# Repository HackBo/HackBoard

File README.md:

HackBoard

Arduino Leonardo compatible board

Un Arduino engallado para hacer mas fáciles y rápidos tus desarrollos. 

Diseñado por y para Geeks . . .

Preview
=========
![Front](
https://github.com/HackBo/HackBoard/blob/master/img/HackBoard.png)

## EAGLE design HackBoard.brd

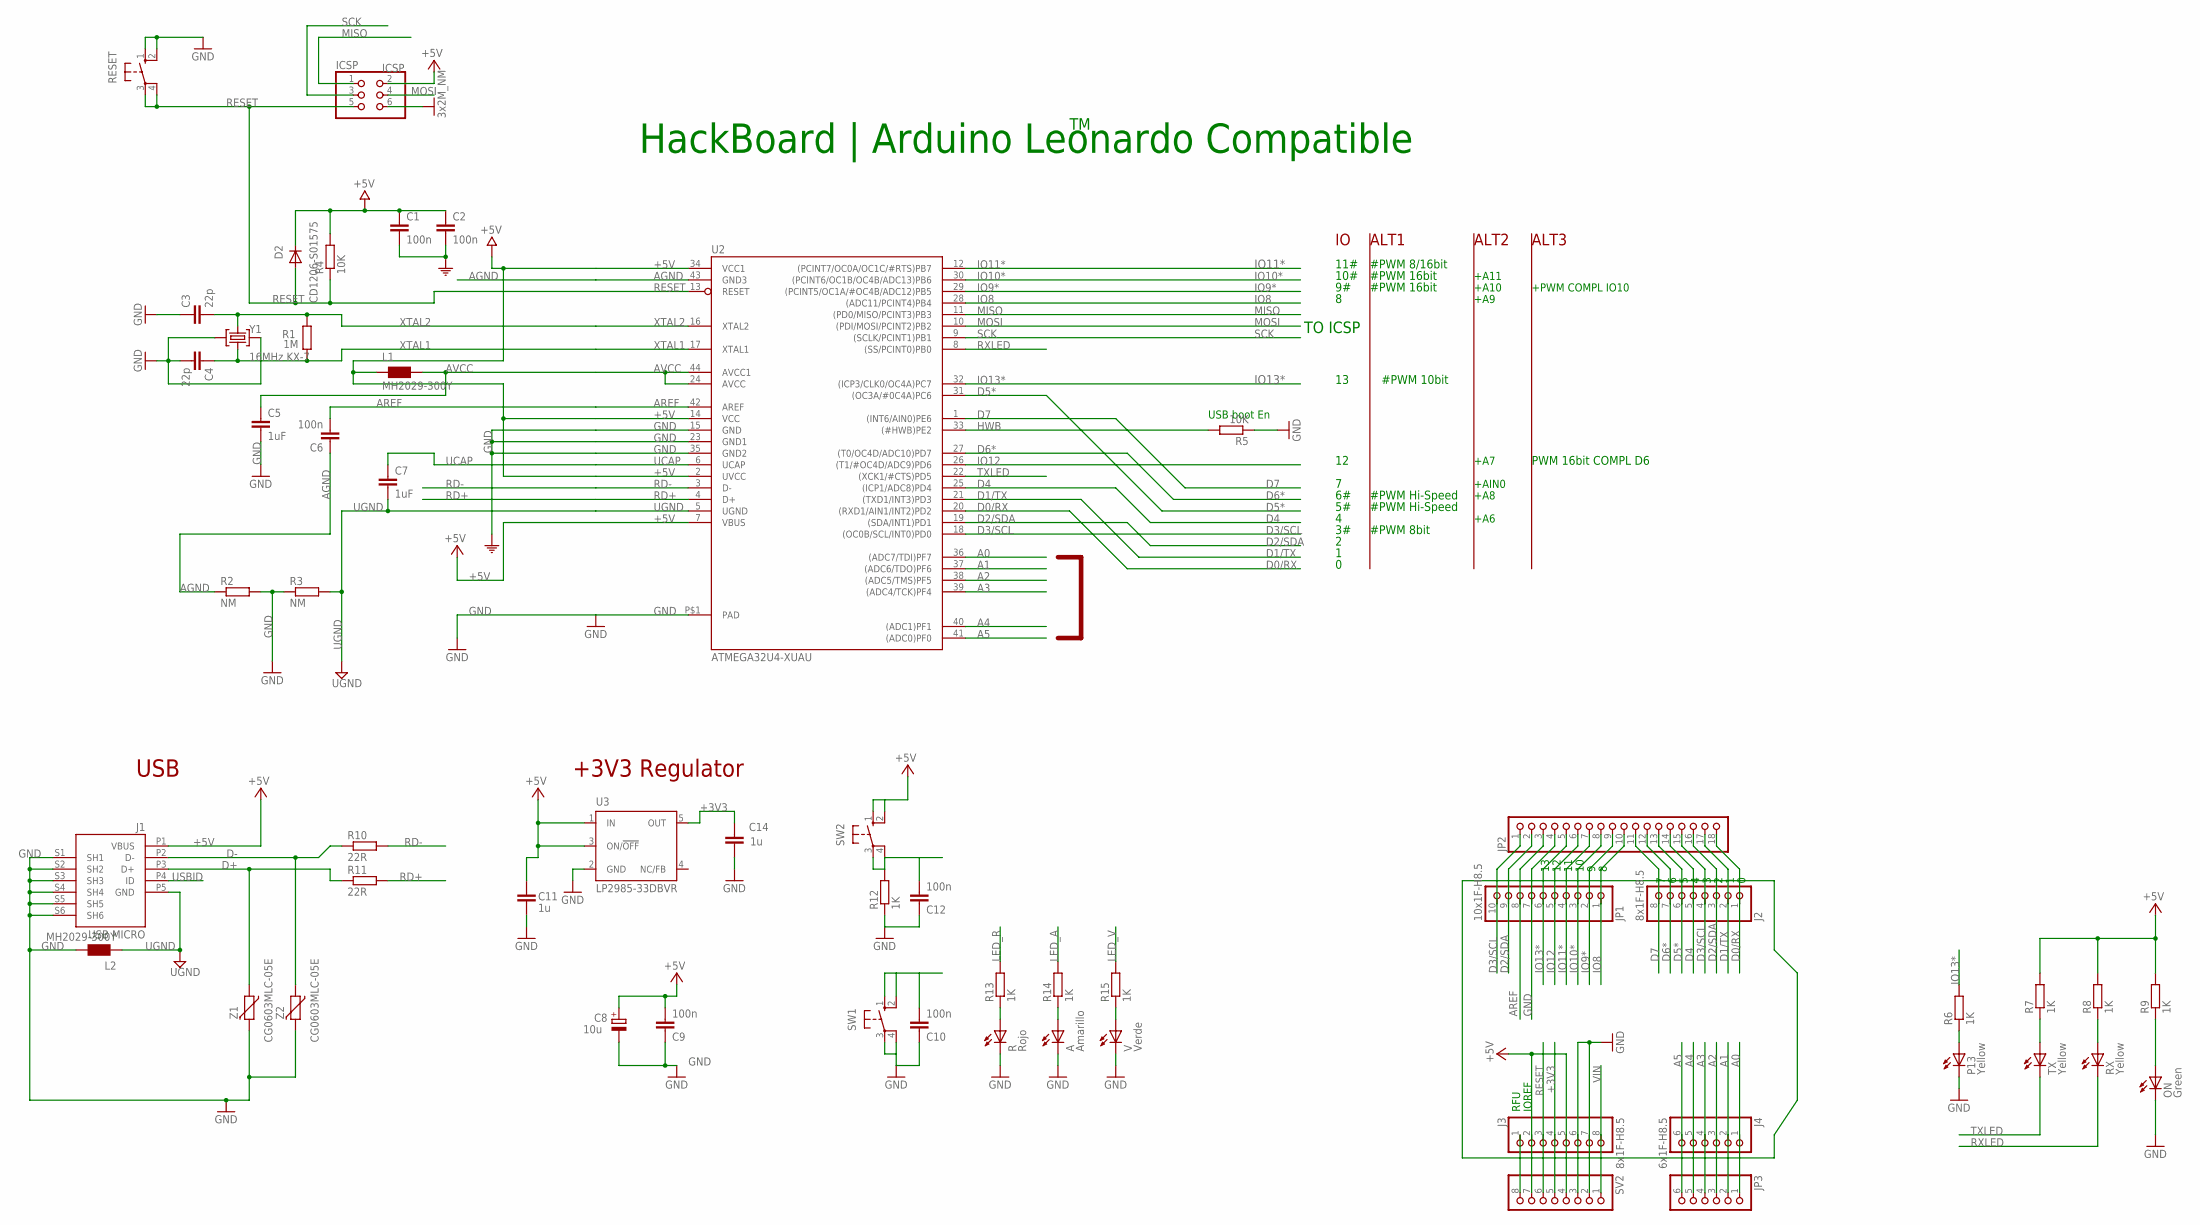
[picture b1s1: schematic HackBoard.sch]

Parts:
A: Amarillo; CHIPLED_0805
C1, C2, C6, C9, C10, C12: 100n; C0805
C3, C4: 22p; C0603-ROUND
C5, C7: 1uF; C0603-ROUND
C8: 10u; SMC_B
C11, C14: 1u; C0603-ROUND
D2: CD1206-S01575; MINIMELF
ICSP: ICSP; 2X03
J1: USB MICRO; CON2_USB_MICRO_B_AT
J2, J3: 8x1F-H8.5; 1X08
J4: 6x1F-H8.5; 1X06
JP1: 10x1F-H8.5; 1X10
JP2: PINHD-1X18; 1X18
JP3: PINHD-1X6; 1X06
L1, L2: MH2029-300Y; 0805
ON: Green; CHIPLED_0805
P13: Yellow; CHIPLED_0805
R: Rojo; CHIPLED_0805
R1: 1M; R0603-ROUND
R2, R3: NM; R0402
R4, R5: 10K; R0805
R6, R7, R8, R9, R12, R13, R14, R15: 1K; M0805
R10, R11: 22R; M0805
RESET: 10-XX; B3F-10XX
RX: Yellow; CHIPLED_0805
SV2: PINHD-1X8; 1X08
SW1, SW2: 10-XX; B3F-10XX
TX: Yellow; CHIPLED_0805
U2: ATMEGA32U4-XUAU; TQFP44-PAD
U3: LP2985-33DBVR; SOT23-DBV
V: Verde; CHIPLED_0805
Y1: 16MHz KX-7; CRYSTAL-3.2-2.5
Z1, Z2: CG0603MLC-05E; CT/CN0603

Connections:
+3V3: C14.2, J3.4, SV2.5, U3.5 (OUT)
+5V: C1.1, C2.1, C8.+, C9.2, C11.2, D2.C, ICSP.2, J1.P1 (VBUS), J3.2, J3.5, L1.1, R4.2, R7.2, R8.2, R9.2, SV2.4, SV2.7, SW2.1 (S), SW2.2 (S1), U2.2 (UVCC), U2.7 (VBUS), U2.14 (VCC), U2.34 (VCC1), U3.1 (IN), U3.3 (ON/!OFF)
A0: J4.1, JP3.1, U2.36 ((ADC7/TDI)PF7)
A1: J4.2, JP3.2, U2.37 ((ADC6/TDO)PF6)
A2: J4.3, JP3.3, U2.38 ((ADC5/TMS)PF5)
A3: J4.4, JP3.4, U2.39 ((ADC4/TCK)PF4)
A4: J4.5, JP3.5, U2.40 ((ADC1)PF1)
A5: J4.6, JP3.6, U2.41 ((ADC0)PF0)
AGND: C6.1, R2.1, U2.43 (GND3)
AREF: C6.2, JP1.8, JP2.3, U2.42 (AREF)
AVCC: C5.1, L1.2, U2.24 (AVCC), U2.44 (AVCC1)
D0/RX: J2.1, JP2.18, U2.20 ((RXD1/AIN1/INT2)PD2)
D1/TX: J2.2, JP2.17, U2.21 ((TXD1/INT3)PD3)
D2/SDA: J2.3, JP1.9, JP2.2, JP2.16, U2.19 ((SDA/INT1)PD1)
D3/SCL: J2.4, JP1.10, JP2.1, JP2.15, U2.18 ((OC0B/SCL/INT0)PD0)
D4: J2.5, JP2.14, U2.25 ((ICP1/ADC8)PD4)
D5*: J2.6, JP2.13, U2.31 ((OC3A/#0C4A)PC6)
D6*: J2.7, JP2.12, U2.27 ((T0/OC4D/ADC10)PD7)
D7: J2.8, JP2.11, U2.1 ((INT6/AIN0)PE6)
D+: J1.P3 (D+), R11.1, Z1.1
D-: J1.P2 (D-), R10.1, Z2.1
GND: A.C, C1.2, C2.2, C3.1, C4.2, C5.2, C8.-, C9.1, C10.1, C11.1, C12.1, C14.1, ICSP.6, J1.S1 (SH1), J1.S2 (SH2), J1.S3 (SH3), J1.S4 (SH4), J1.S5 (SH5), J1.S6 (SH6), J3.6, J3.7, JP1.7, JP2.4, L2.2, ON.C, P13.C, R.C, R2.2, R3.1, R5.1, R12.1, RESET.1 (S), RESET.2 (S1), SV2.2, SV2.3, SW1.3, SW1.4 (P1), U2.15 (GND), U2.23 (GND1), U2.35 (GND2), U2.P$1 (PAD), U3.2 (GND), V.C, Y1.2 (GND), Y1.4 (GND), Z1.2, Z2.2
HWB: R5.2, U2.33 ((#HWB)PE2)
IO8: JP1.1, JP2.10, U2.28 ((ADC11/PCINT4)PB4)
IO9*: JP1.2, JP2.9, U2.29 ((PCINT5/OC1A/#OC4B/ADC12)PB5)
IO10*: JP1.3, JP2.8, U2.30 ((PCINT6/OC1B/OC4B/ADC13)PB6)
IO11*: JP1.4, JP2.7, U2.12 ((PCINT7/OC0A/OC1C/#RTS)PB7)
IO12: JP1.5, JP2.6, U2.26 ((T1/#OC4D/ADC9)PD6)
IO13*: JP1.6, JP2.5, R6.2, U2.32 ((ICP3/CLK0/OC4A)PC7)
LED_A: R14.2
LED_R: R13.2
LED_V: R15.2
MISO: ICSP.1, U2.11 ((PD0/MISO/PCINT3)PB3)
MOSI: ICSP.4, U2.10 ((PDI/MOSI/PCINT2)PB2)
unnamed: R7.1, TX.A
unnamed: P13.A, R6.1
unnamed: ON.A, R9.1
unnamed: R8.1, RX.A
unnamed: J3.1, SV2.8
unnamed: R.A, R13.1
unnamed: A.A, R14.1
unnamed: R15.1, V.A
RD+: R11.2, U2.4 (D+)
RD-: R10.2, U2.3 (D-)
RESET: D2.A, ICSP.5, J3.3, R4.1, RESET.3, RESET.4 (P1), SV2.6, U2.13 (RESET)
RXLED: RX.C, U2.8 ((SS/PCINT0)PB0)
SCK: ICSP.3, U2.9 ((SCLK/PCINT1)PB1)
SW1: C10.2, SW1.1 (S), SW1.2 (S1)
SW2: C12.2, R12.2, SW2.3, SW2.4 (P1)
TXLED: TX.C, U2.22 ((XCK1/#CTS)PD5)
UCAP: C7.1, U2.6 (UCAP)
UGND: C7.2, J1.P5 (GND), L2.1, R3.2, U2.5 (UGND)
USBID: J1.P4 (ID)
VIN: J3.8, SV2.1
XTAL1: C4.1, R1.1, U2.17 (XTAL1), Y1.1 (C1)
XTAL2: C3.2, R1.2, U2.16 (XTAL2), Y1.3 (C2)

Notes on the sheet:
HackBoard | Arduino Leonardo Compatible
USB boot En
USB
+3V3 Regulator
TO ICSP
10#
11#
#PWM 8bit
#PWM Hi-Speed
#PWM 8/16bit
#PWM 16bit
PWM 16bit COMPL D6
#PWM 10bit
+A6
+A7
IOREF
RFU
+A11
+A10
+A8
+A9
+PWM COMPL IO10
+AIN0
ALT1
ALT2
ALT3

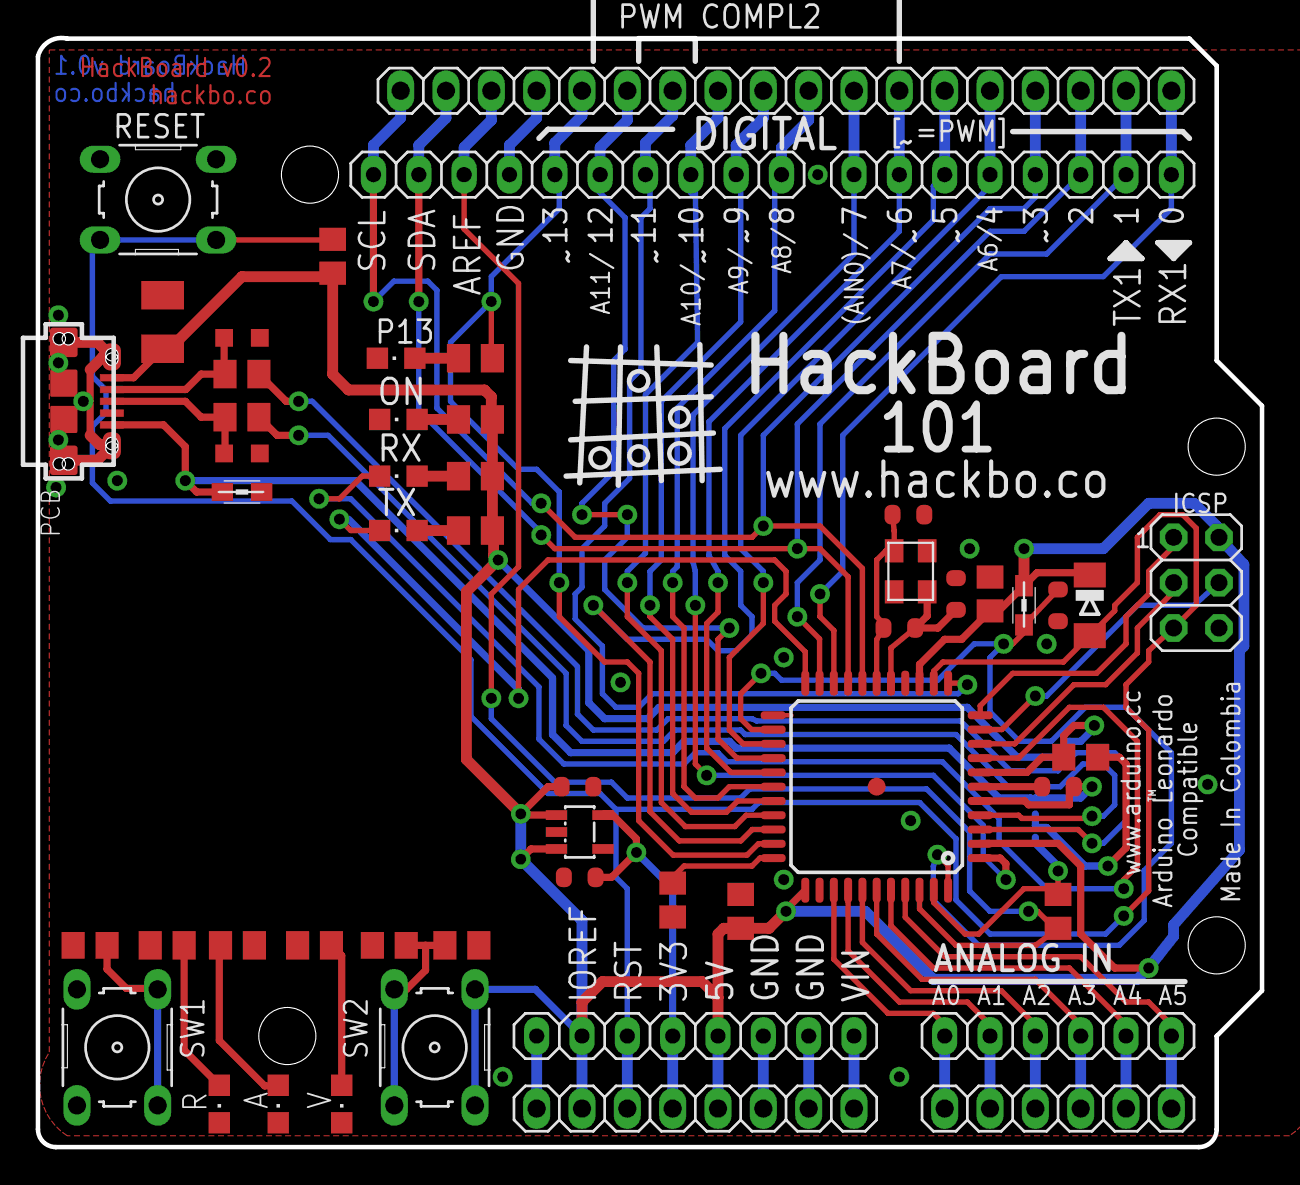
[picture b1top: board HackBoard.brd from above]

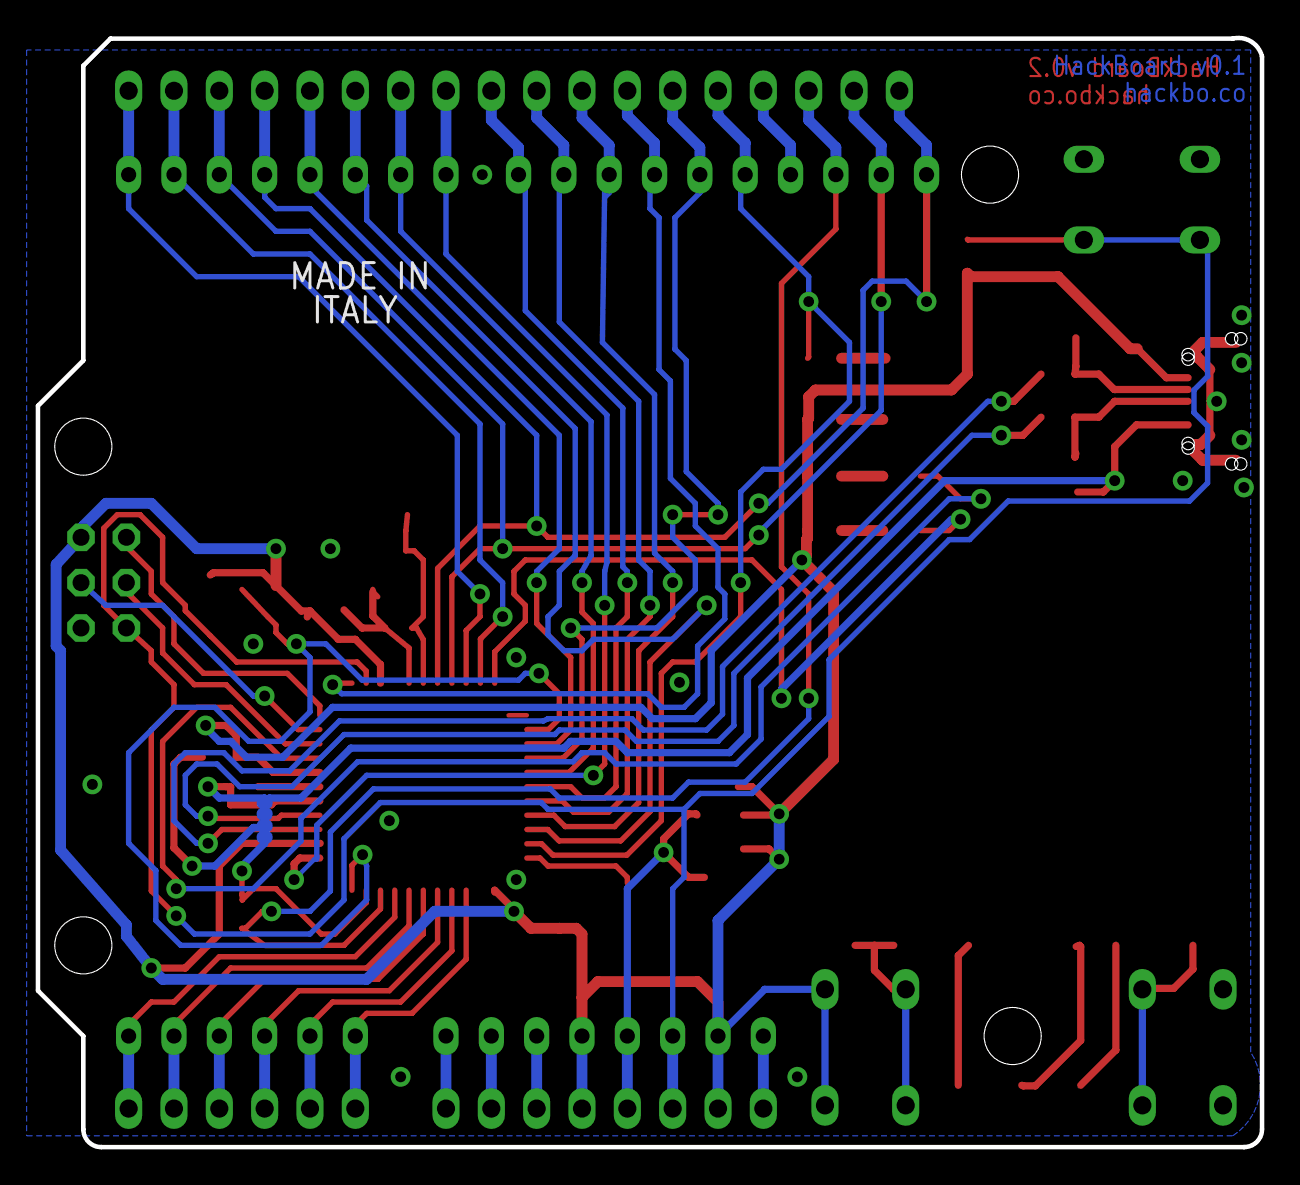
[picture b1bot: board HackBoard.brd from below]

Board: 2 copper layers, 68.6 x 62.1 mm, 55 parts (2 on the bottom side), 52 nets.

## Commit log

2014-08-28 first preliminary version
2014-08-28 Versión 0.1
2014-08-30 Adición de 2 switch y 3 leds
2014-10-29 Se elimina Micro con encapsulado QFN
2014-10-29 Se actualiza esquematico
2014-10-29 Se modifica el nombre de la tarjeta a HackBoard 101
2014-10-29 Se adicionda la carpeta img para almacenar los render
2014-10-29 Se adicionda la carpeta gerber y se crean los primeros archivos gerber
2014-10-29 Se actualiza la imagen de render
2014-10-29 Se actualiza el readme con una imagen de render
